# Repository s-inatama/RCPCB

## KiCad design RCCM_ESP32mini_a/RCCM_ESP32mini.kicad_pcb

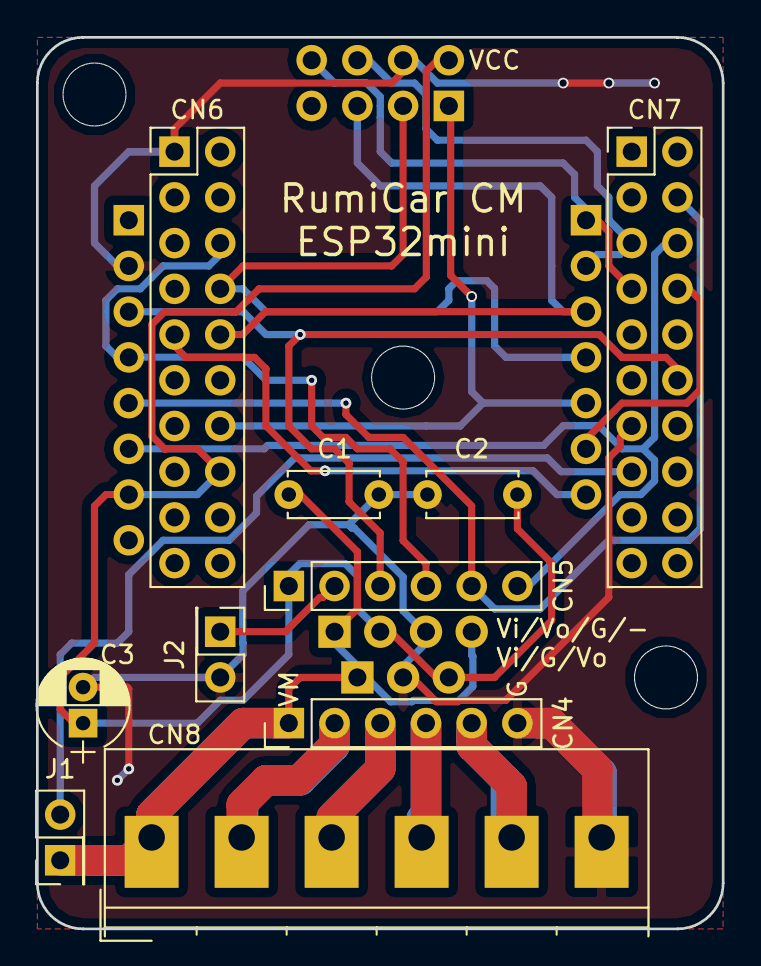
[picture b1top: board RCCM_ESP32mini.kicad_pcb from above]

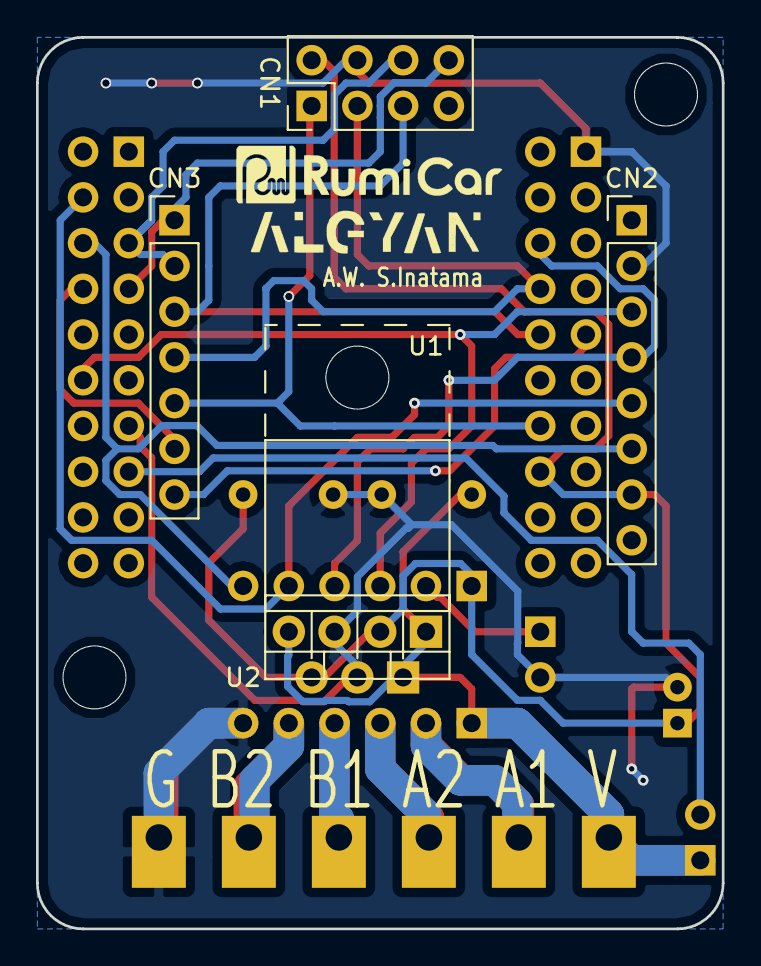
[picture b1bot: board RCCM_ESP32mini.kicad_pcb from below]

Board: 2 copper layers, 38.1 x 49.5 mm, 20 parts (8 on the bottom side), 20 nets.

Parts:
C1: 104; C_Disc_D5.0mm_W2.5mm_P5.00mm
C2: 105; C_Disc_D5.0mm_W2.5mm_P5.00mm
C3: 100u; CP_Radial_D5.0mm_P2.00mm
CN1: Conn_02x04_Odd_Even; Pin_Header_Straight_2x04_Pitch2.54mm
CN2: Conn_01x08; Pin_Header_Straight_1x08_Pitch2.54mm
CN3: Conn_01x07; Pin_Header_Straight_1x07_Pitch2.54mm
CN4, CN5: Conn_01x06; Pin_Header_Straight_1x06_Pitch2.54mm
CN6, CN7: Conn_02x10_Odd_Even; Pin_Header_Straight_2x10_Pitch2.54mm
CN8: Conn_01x06; TerminalBlock_Philmore_TB13x_06x5mm_Straight
H1, H2: MountingHole_3.5mm
J1, J2: Conn_01x02; Pin_Header_Straight_2x01_Pitch2.54mm
L1: LOGO; RumiCar1_3p3
L2: LOGO; RumiCar3_3p3
L3: LOGO; ALGYAN2p5
U1: LT1129-3.3_SOT223; TO-220_Horizontal_Reversed
U2: KA378R33; TO-220-4_Vertical

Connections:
3V3e: C2.1, C3.1, CN1.2, CN2.7, CN5.1, CN6.16, U1.3, U2.2
AIN1: CN2.3, CN5.3, CN7.12
AIN2: CN2.4, CN5.4, CN6.6
Aout1: CN4.2, CN8.2
Aout2: CN4.3, CN8.3
BIN1: CN2.5, CN5.5, CN7.4
BIN2: CN2.6, CN5.6, CN7.6
Bout1: CN4.4, CN8.4
Bout2: CN4.5, CN8.5
GND: C1.2, C2.2, C3.2, CN1.4, CN2.2, CN4.6, CN6.1, CN7.13, CN8.6, J2.2, U1.2, U2.3
IO05: CN1.1, CN3.5, CN6.14
IO18: CN1.3, CN3.4, CN6.8
IO19: CN1.5, CN3.3, CN6.10
IO21: CN1.8, CN3.1, CN7.7
IO22: CN1.6, CN3.2, CN7.5
IO32: CN3.6, CN7.8
IO33: CN3.7, CN6.9
MODEd: CN5.2, J2.1
VCCe: CN7.15, J1.2
Vin: C1.1, CN2.1, CN4.1, CN8.1, J1.1, U1.1, U2.1, U2.4

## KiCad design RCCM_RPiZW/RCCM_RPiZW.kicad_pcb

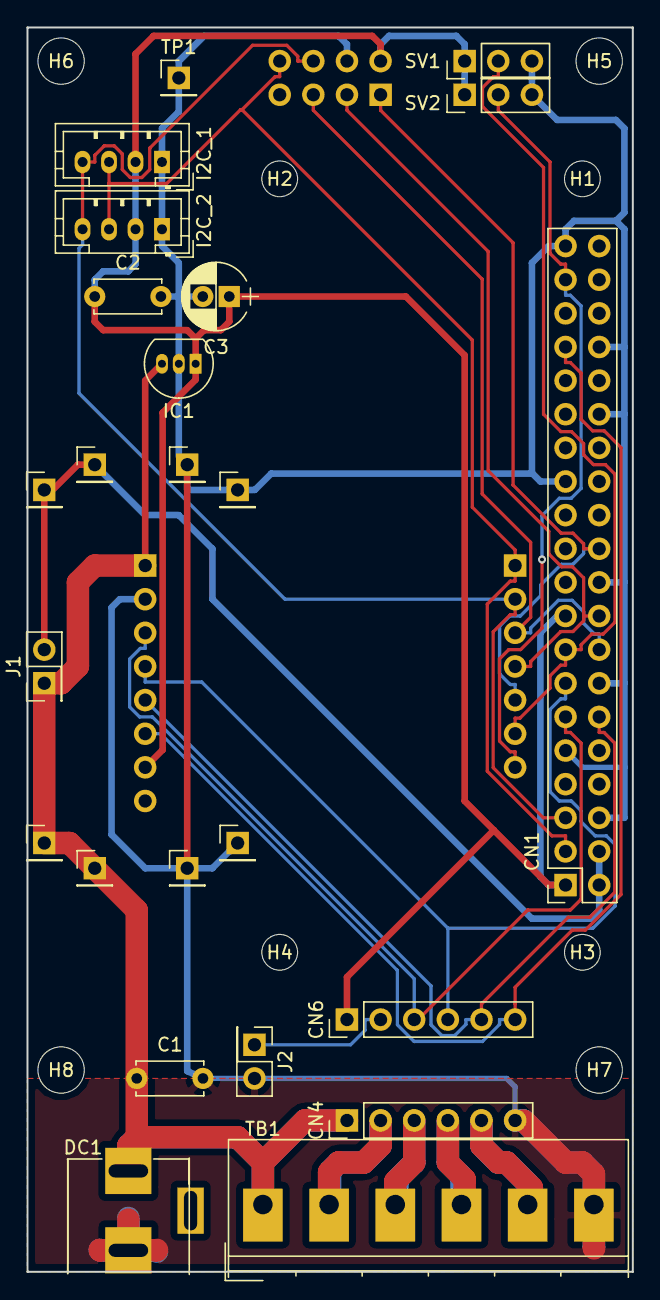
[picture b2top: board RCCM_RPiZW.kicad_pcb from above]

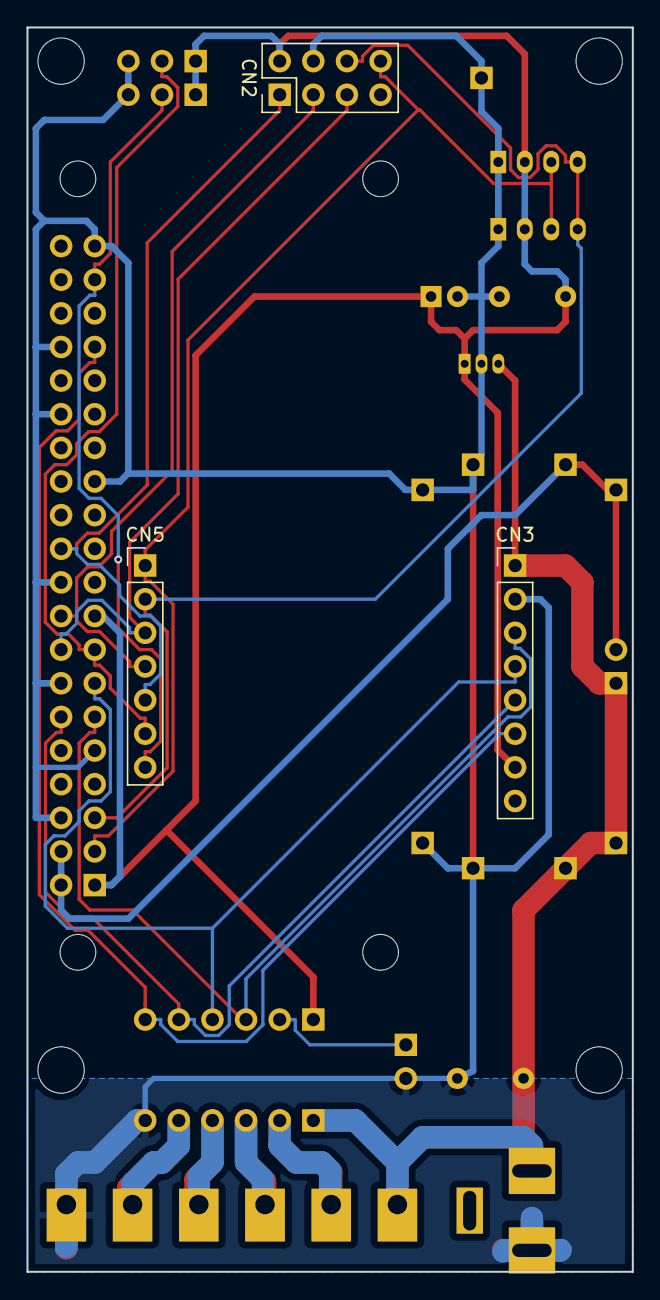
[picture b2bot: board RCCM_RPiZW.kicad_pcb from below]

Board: 2 copper layers, 45.7 x 94.0 mm, 35 parts (3 on the bottom side), 20 nets.

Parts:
C1: 104; C_Disc_D5.0mm_W2.5mm_P5.00mm
C2: 105; C_Disc_D5.0mm_W2.5mm_P5.00mm
C3: 100u; CP_Radial_D5.0mm_P2.00mm
CN1: Conn_02x20_Odd_Even; Socket_Strip_Straight_2x20_Pitch2.54mm
CN2: Conn_02x04_Odd_Even; Pin_Header_Straight_2x04_Pitch2.54mm
CN3: Conn_01x08; Pin_Header_Straight_1x08_Pitch2.54mm
CN4, CN6: Conn_01x06; Pin_Header_Straight_1x06_Pitch2.54mm
CN5: Conn_01x07; Pin_Header_Straight_1x07_Pitch2.54mm
DC1: Jack-DC; BARREL_JACK_NoSilk
DC1-1, DC1-2, DC1-3, DC1-4, DC1-5, DC1-6, DC1-7, DC1-8: Conn_01x01; Pin_Header_Straight_1x01_Pitch2.54mm
H1, H2, H3, H4: M2.7; MountingHole_2.7mm_M2.5
H5, H6, H7, H8: M3.5; MountingHole_3.5mm
I2C_1, I2C_2: Conn_01x04; JST_PH_B4B-PH-K_04x2.00mm_Straight
IC1: LP2950-3.0_TO92; TO-92_Inline_Narrow_Oval
J1, J2: Conn_01x02; Pin_Header_Straight_2x01_Pitch2.54mm
SV1, SV2: Conn_01x03; Pin_Header_Straight_1x03_Pitch2.54mm
TB1: Conn_01x06; TerminalBlock_Philmore_TB13x_06x5mm_Straight
TP1: Conn_01x01; Pin_Header_Straight_1x01_Pitch2.54mm

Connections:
3V3: C2.1, C3.1, CN1.1, CN1.17, CN2.2, CN3.7, CN6.1, I2C_1.2, I2C_2.2, IC1.1, SV1.1, SV2.1
+5V: CN1.2, CN1.4, DC1-5.1, DC1-6.1, J1.2
AIN1: CN1.11, CN3.3, CN6.3
AIN2: CN1.13, CN3.4, CN6.4
Aout1: CN4.2, TB1.2
Aout2: CN4.3, TB1.3
BIN1: CN1.12, CN3.5, CN6.5
BIN2: CN1.33, CN3.6, CN6.6
Bout1: CN4.4, TB1.4
Bout2: CN4.5, TB1.5
GND: C1.2, C2.2, C3.2, CN1.6, CN1.9, CN1.14, CN1.20, CN1.25, CN1.30, CN1.34, CN1.39, CN2.4, CN3.2, CN4.6, DC1.2, DC1-3.1, DC1-4.1, DC1-7.1, DC1-8.1, I2C_1.1, I2C_2.1, IC1.2, J2.2, SV1.3, SV2.3, TB1.6, TP1.1
GP02: CN1.3, CN2.8, CN5.1, I2C_1.3, I2C_2.3
GP03: CN1.5, CN2.6, CN5.2, I2C_1.4, I2C_2.4
GP22: CN1.15, CN5.6, SV1.2
GP23: CN1.16, CN2.5, CN5.3
GP24: CN1.18, CN2.3, CN5.4
GP25: CN1.22, CN2.1, CN5.5
GP26: CN1.37, CN5.7, SV2.2
MODEd: CN6.2, J2.1
VBat: C1.1, CN3.1, CN4.1, DC1.1, DC1-1.1, DC1-2.1, IC1.3, J1.1, TB1.1

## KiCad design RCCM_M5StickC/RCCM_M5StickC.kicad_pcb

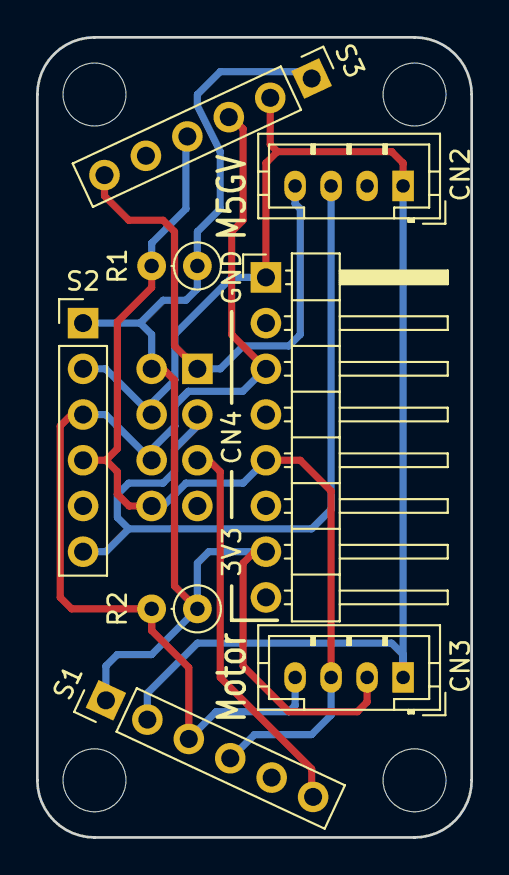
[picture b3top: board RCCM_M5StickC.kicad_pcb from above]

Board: 2 copper layers, 24.1 x 44.5 mm, 13 parts (1 on the bottom side), 7 nets.

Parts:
CN1: Conn_02x04_Odd_Even; Pin_Header_Straight_2x04_Pitch2.54mm
CN2, CN3: Conn_01x04; JST_PH_B4B-PH-K_04x2.00mm_Straight
CN4: Conn_01x08; Pin_Header_Angled_1x08_Pitch2.54mm
H1, H2, H3, H4: MountingHole_3.5mm
R1, R2: R; R_Axial_DIN0207_L6.3mm_D2.5mm_P2.54mm_Vertical
S1, S2, S3: Conn_01x06; Pin_Header_Straight_1x06_Pitch2.54mm

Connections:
3V3m: CN1.2, CN3.2, CN4.7, R1.1, R2.1, S1.1, S2.1, S3.1
G00: CN1.8, CN3.3, CN4.5, R1.2, S1.4, S2.4, S3.4
G26: CN1.6, CN3.4, CN4.3, R2.2, S1.3, S2.3, S3.3
G32: CN1.3, CN2.3, S2.6
G33: CN1.1, CN2.4, S3.6
GND: CN1.4, CN2.1, CN3.1, CN4.1, S1.2, S2.2, S3.2
SD0: CN1.5, S1.6

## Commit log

2020-05-16 Add CM
    Add ESP32 CM & M5StikC CM
2020-05-16 ADD pdf
2020-05-17 Add gerber
2020-05-19 Gerber change
2020-05-27 Gerber Update
2020-05-29 SDx Update
    (No:Pos:SDx:CNx:Nano:ESP32:M5S),
    (S1:LEFT:SD0:CN1-5:No14:IO19:NC),
    (S2:CEN:SD1:CN1-3:No15:IO18:G32),
    (S3:RIGHT:SD2:CN1-1:No16:IO5:G33)
2020-06-11 Add Panelized Gerber
    xxx-Gerber-P is Panelized data.
2020-06-18 Add RPiZW
2020-06-20 ADD RPiZW image
2020-06-23 Update RPiZW Gerber
2020-08-07 Small changes
    M5Stick-C Rev.a
    ESP32 None
    RasPi ZW Change gerber
2020-08-20 Rev.A
